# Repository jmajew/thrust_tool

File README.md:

# ThrustTool #

The ThrustTool is a DIY tool for measurements of an electric motor with propeller.
It allows to measure thrust, torque, rotation speed, battery voltage and current.

The project is by no means finished (especially firmware thrust++ and ThrustApp). However in current stage it works quite well allowing to obtain the results
(e.g., see auto generated report (in latex) [T-Motor F1507 with t3140 propeller](ThrustApp/data/tmotor-f1507/f1507_t3140_4s.pdf)).

### The project includes:

* [the 3d-printed tool](Doc/Tool.md)
* [custom board based on STM32 F401 mcu](Doc/Board.md)
* [firmware for the custom board](Doc/Firmware.md)
* [QT application for measurement managing and reporting](Doc/ThrustApp.md)

### 3D render of the tool

## Warning ##

The project is delivered as is. All responsibilities lies on the side of the user. 
Remember to take adequate security measures when testing any motor (especially powerful one).

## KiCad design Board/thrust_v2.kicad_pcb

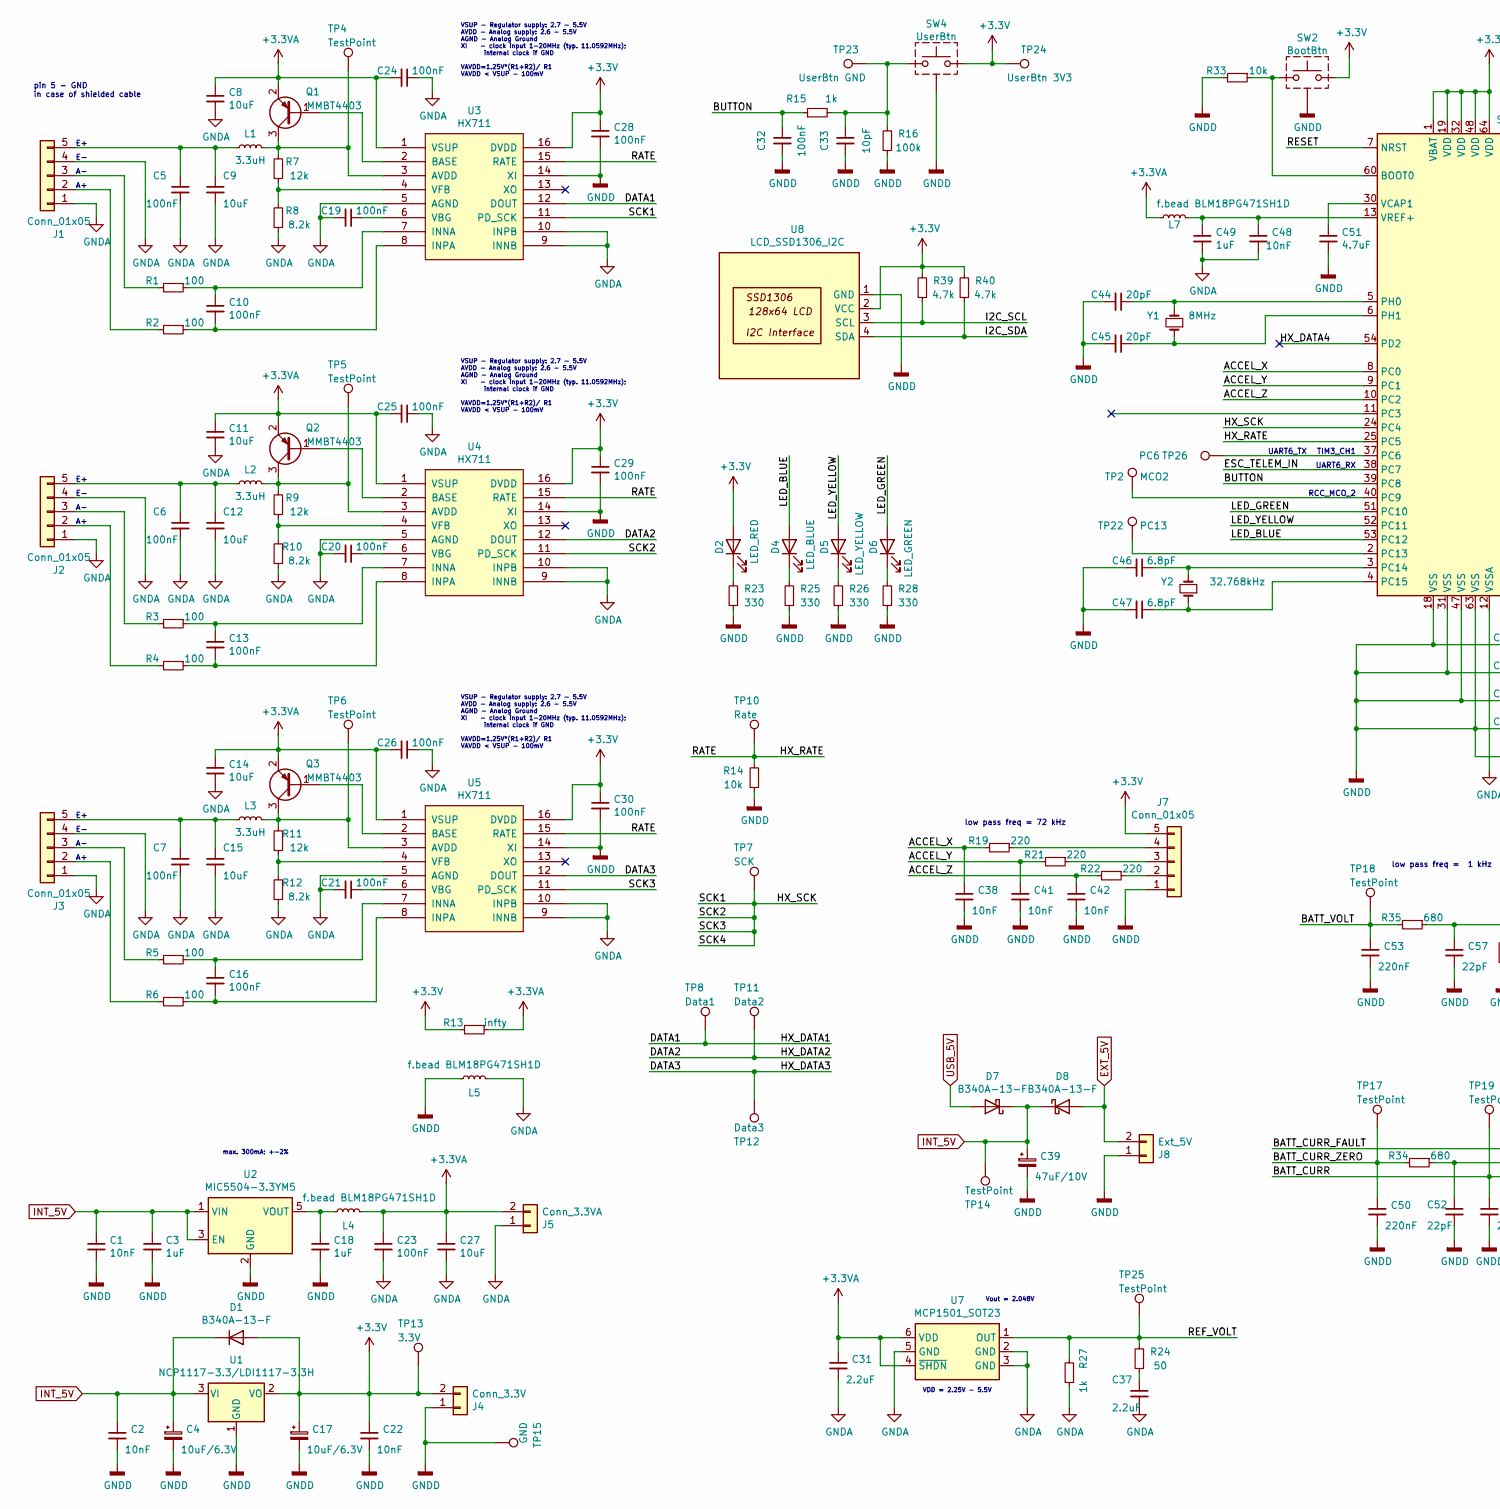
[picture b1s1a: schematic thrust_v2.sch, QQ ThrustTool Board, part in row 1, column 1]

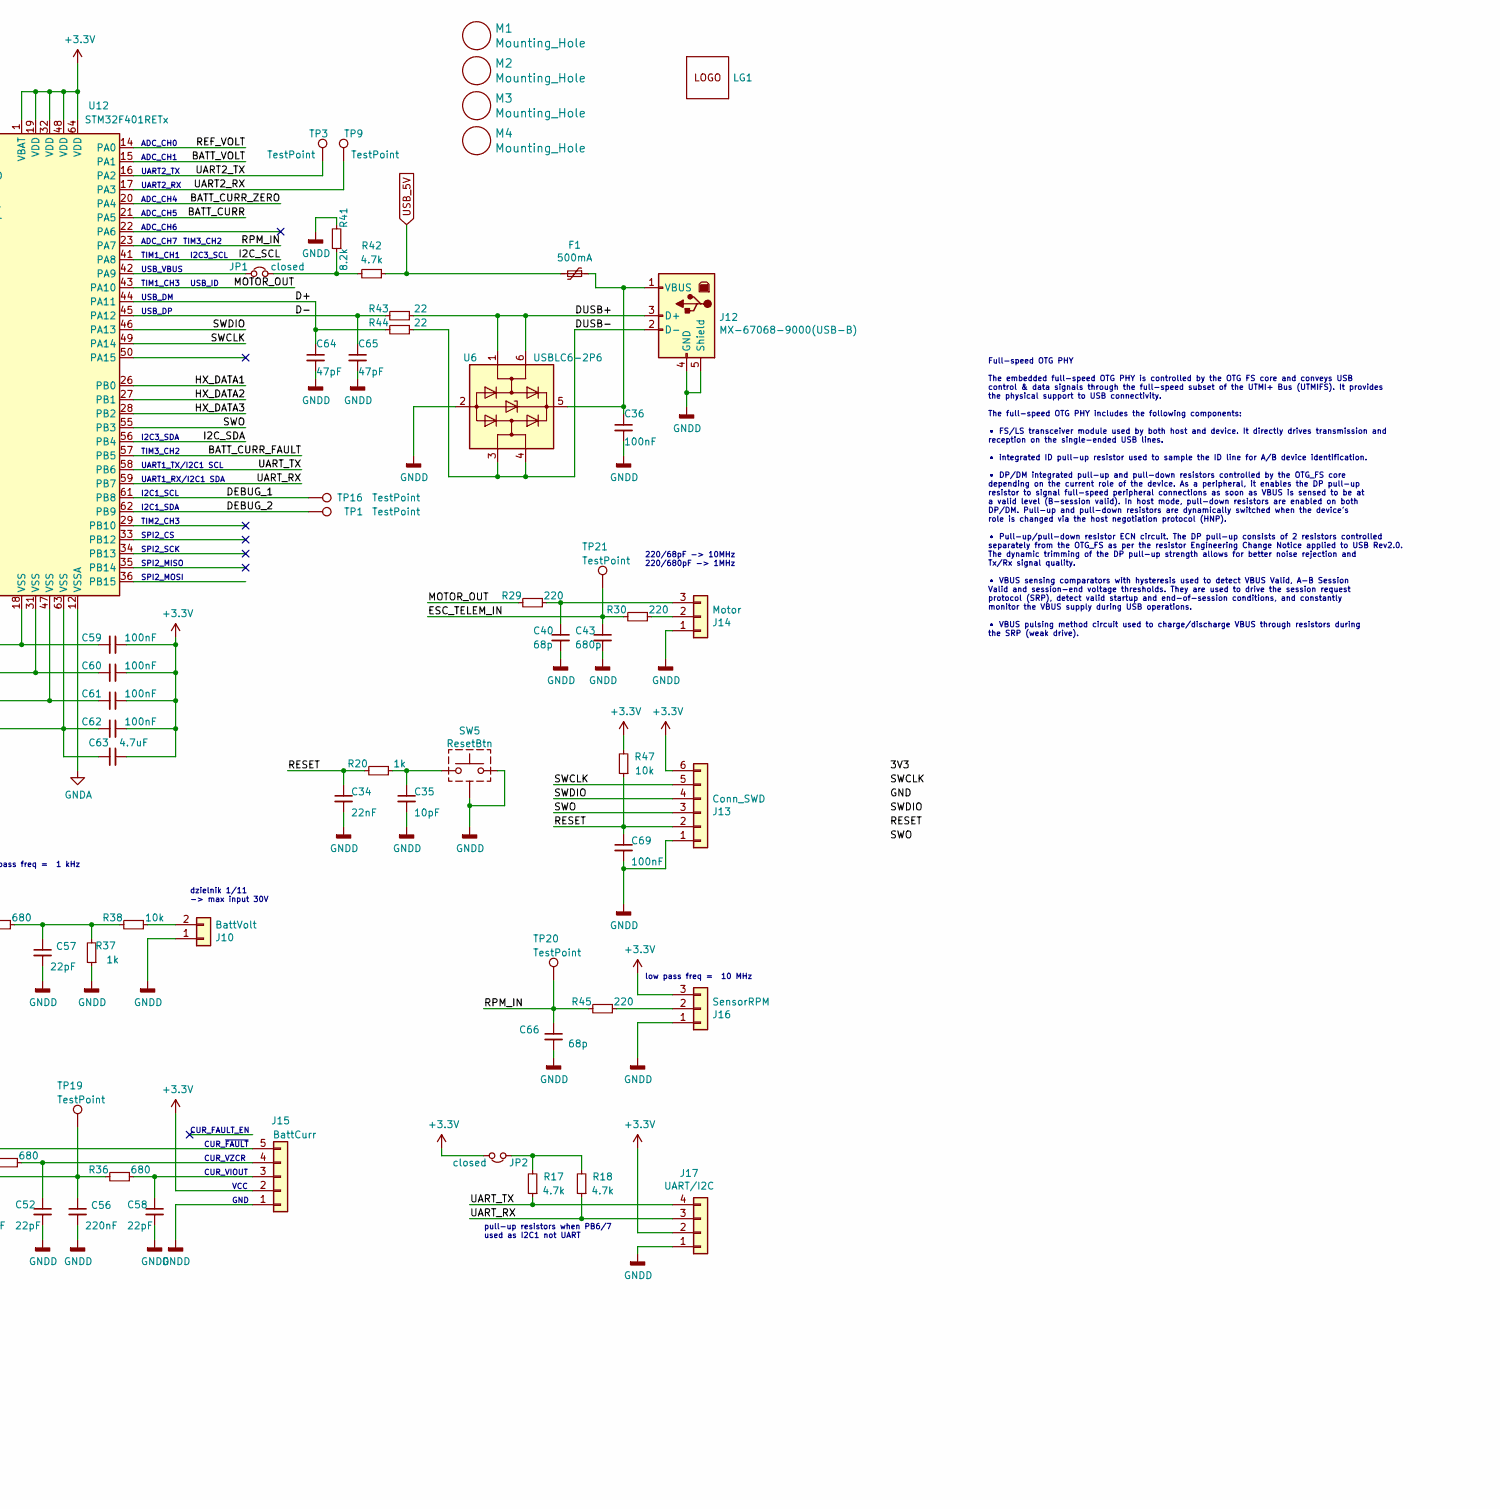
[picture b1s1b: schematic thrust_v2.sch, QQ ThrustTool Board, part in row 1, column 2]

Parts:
C1, C2, C22, C38, C41, C42, C48: 10nF; C_0603_1608Metric_Pad1.08x0.95mm_HandSolder
C3, C18, C49: 1uF; C_0603_1608Metric_Pad1.08x0.95mm_HandSolder
C4, C17: 10uF/6.3V; CP_EIA-3528-21_Kemet-B_Pad1.50x2.35mm_HandSolder
C5, C6, C7, C10, C13, C16, C19, C20, C21, C23, C24, C25, C26, C28, C29, C30, C32, C36, C59, C60, C61, C62, C69: 100nF; C_0603_1608Metric_Pad1.08x0.95mm_HandSolder
C8, C9, C11, C12, C14, C15, C27: 10uF; C_0603_1608Metric_Pad1.08x0.95mm_HandSolder
C31, C37: 2.2uF; C_0603_1608Metric_Pad1.08x0.95mm_HandSolder
C33, C35: 10pF; C_0603_1608Metric_Pad1.08x0.95mm_HandSolder
C34: 22nF; C_0603_1608Metric_Pad1.08x0.95mm_HandSolder
C39: 47uF/10V; CP_EIA-3528-21_Kemet-B_Pad1.50x2.35mm_HandSolder
C40, C66: 68p; C_0603_1608Metric_Pad1.08x0.95mm_HandSolder
C43: 680p; C_0603_1608Metric_Pad1.08x0.95mm_HandSolder
C44, C45: 20pF; C_0603_1608Metric_Pad1.08x0.95mm_HandSolder
C46, C47: 6.8pF; C_0603_1608Metric_Pad1.08x0.95mm_HandSolder
C50, C53, C56: 220nF; C_0603_1608Metric_Pad1.08x0.95mm_HandSolder
C51, C63: 4.7uF; C_0603_1608Metric_Pad1.08x0.95mm_HandSolder
C52, C57, C58: 22pF; C_0603_1608Metric_Pad1.08x0.95mm_HandSolder
C64, C65: 47pF; C_0603_1608Metric_Pad1.08x0.95mm_HandSolder
D1, D7, D8: B340A-13-F; D_SMA
D2: LED_RED; LED_0603_1608Metric_Pad1.05x0.95mm_HandSolder
D4: LED_BLUE; LED_0603_1608Metric_Pad1.05x0.95mm_HandSolder
D5: LED_YELLOW; LED_0603_1608Metric_Pad1.05x0.95mm_HandSolder
D6: LED_GREEN; LED_0603_1608Metric_Pad1.05x0.95mm_HandSolder
F1: 500mA; Fuse_0805_2012Metric_Pad1.15x1.40mm_HandSolder
J1, J2, J3, J7: Conn_01x05; PinHeader_1x05_P2.54mm_Vertical
J4: Conn_3.3V; PinHeader_1x02_P2.54mm_Vertical
J5: Conn_3.3VA; PinHeader_1x02_P2.54mm_Vertical
J8: Ext_5V; PinHeader_1x02_P2.54mm_Vertical
J10: BattVolt; PinHeader_1x02_P2.54mm_Vertical
J12: MX-67068-9000(USB-B); USB_B_OST_USB-B1HSxx_Horizontal_mod
J13: Conn_SWD; PinHeader_1x06_P2.54mm_Vertical
J14: Motor; PinHeader_1x03_P2.54mm_Vertical
J15: BattCurr; PinHeader_1x05_P2.54mm_Vertical
J16: SensorRPM; PinHeader_1x03_P2.54mm_Vertical
J17: UART/I2C; PinHeader_1x04_P2.54mm_Vertical
JP1, JP2: closed; SolderJumper-2_P1.3mm_Open_TrianglePad1.0x1.5mm
L1, L2, L3: 3.3uH; L_0603_1608Metric_Pad1.05x0.95mm_HandSolder
L4, L5, L7: f.bead BLM18PG471SH1D; L_0603_1608Metric_Pad1.05x0.95mm_HandSolder
LG1: Logo_1; LOGO_QX4_knot_circ2_24mm
M1, M2, M3, M4: Mounting_Hole; MountingHole_3.2mm_M3
Q1, Q2, Q3: MMBT4403; SOT-23
R1, R2, R3, R4, R5, R6: 100; R_0603_1608Metric_Pad0.98x0.95mm_HandSolder
R7, R9, R11: 12k; R_0603_1608Metric_Pad0.98x0.95mm_HandSolder
R8, R10, R12, R41: 8.2k; R_0603_1608Metric_Pad0.98x0.95mm_HandSolder
R13: infty; R_0603_1608Metric_Pad0.98x0.95mm_HandSolder
R14, R33, R38, R47: 10k; R_0603_1608Metric_Pad0.98x0.95mm_HandSolder
R15, R20, R27, R37: 1k; R_0603_1608Metric_Pad0.98x0.95mm_HandSolder
R16: 100k; R_0603_1608Metric_Pad0.98x0.95mm_HandSolder
R17, R18, R39, R40, R42: 4.7k; R_0603_1608Metric_Pad0.98x0.95mm_HandSolder
R19, R21, R22, R29, R30, R45: 220; R_0603_1608Metric_Pad0.98x0.95mm_HandSolder
R23, R25, R26, R28: 330; R_0603_1608Metric_Pad0.98x0.95mm_HandSolder
R24: 50; R_0603_1608Metric_Pad0.98x0.95mm_HandSolder
R34, R35, R36: 680; R_0603_1608Metric_Pad0.98x0.95mm_HandSolder
R43, R44: 22; R_0603_1608Metric_Pad0.98x0.95mm_HandSolder
SW2: BootBtn; SW_Push_1P1T-SH_NO_CK_KMR2xxG
SW4: UserBtn; SW_SPST_Panasonic_EVQPL_3PL_5PL_PT_A15
SW5: ResetBtn; SW_Push_1P1T-SH_NO_CK_KMR2xxG
TP1, TP3, TP9, TP14, TP16, TP17, TP18, TP19, TP20, TP21: TestPoint; TestPoint_Pad_1.5x1.5mm
TP2: MCO2; TestPoint_Pad_1.5x1.5mm
TP4, TP5, TP6, TP25: TestPoint; TestPoint_Pad_D1.0mm
TP7: SCK; TestPoint_Pad_1.5x1.5mm
TP8: Data1; TestPoint_Pad_1.5x1.5mm
TP10: Rate; TestPoint_Pad_1.5x1.5mm
TP11: Data2; TestPoint_Pad_1.5x1.5mm
TP12: Data3; TestPoint_Pad_1.5x1.5mm
TP13: 3.3V; TestPoint_Pad_1.5x1.5mm
TP15: GND; TestPoint_Pad_1.5x1.5mm
TP22: PC13; TestPoint_Pad_1.5x1.5mm
TP23: UserBtn GND; TestPoint_Pad_1.5x1.5mm
TP24: UserBtn 3V3; TestPoint_Pad_1.5x1.5mm
TP26: PC6; TestPoint_Pad_1.5x1.5mm
U1: NCP1117-3.3/LDI1117-3.3H; SOT-223-3_TabPin2
U2: MIC5504-3.3YM5; SOT-23-5
U3, U4, U5: HX711; SOIC-16_3.9x9.9mm_P1.27mm
U6: USBLC6-2P6; SOT-23-6
U7: MCP1501_SOT23; SOT-23-6
U8: LCD_SSD1306_I2C; PinHeader_1x04_P2.54mm_Vertical
U12: STM32F401RETx; LQFP-64_10x10mm_P0.5mm
Y1: 8MHz; Crystal_HC49-4H_Vertical
Y2: 32.768kHz; ABS25

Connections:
+3.3VA: C8.1, C11.1, C14.1, C23.1, C24.2, C25.2, C26.2, C27.1, C31.1, J5.2, L4.2, L7.1, Q1.2 (E), Q2.2 (E), Q3.2 (E), R13.1, U3.1 (VSUP), U4.1 (VSUP), U5.1 (VSUP), U7.4 (~SHDN), U7.6 (VDD)
+3V3: C17.1, C22.1, C28.1, C29.1, C30.1, C59.1, C60.1, C61.1, C62.1, C63.1, D1.2 (A), D2.2 (A), J4.2, J7.5, J13.6, J15.2, J16.3, J17.2, JP2.2, R13.2, R39.2, R40.2, R47.2, SW2.2, SW4.2, TP13.1, TP24.1, U1.2 (VO), U3.16 (DVDD), U4.16 (DVDD), U5.16 (DVDD), U8.2 (VCC), U12.1 (VBAT), U12.19 (VDD), U12.32 (VDD), U12.48 (VDD), U12.64 (VDD)
/ACCEL_X: C38.1, R19.2, U12.8 (PC0)
/ACCEL_Y: C41.1, R21.2, U12.9 (PC1)
/ACCEL_Z: C42.1, R22.2, U12.10 (PC2)
/BATT_CURR: C56.1, R36.2, TP19.1, U12.21 (PA5)
/BATT_CURR_FAULT: J15.5, U12.57 (PB5)
/BATT_CURR_ZERO: C50.1, R34.2, TP17.1, U12.20 (PA4)
/BATT_VOLT: C53.1, R35.2, TP18.1, U12.15 (PA1)
/BUTTON: C32.1, R15.1, U12.39 (PC8)
/D+: C64.1, R44.2, U12.44 (PA11)
/D-: C65.1, R43.2, U12.45 (PA12)
/DATA1: TP8.1, U3.12 (DOUT), U12.26 (PB0)
/DATA2: TP11.1, U4.12 (DOUT), U12.27 (PB1)
/DATA3: TP12.1, U5.12 (DOUT), U12.28 (PB2)
/DEBUG_1: TP16.1, U12.61 (PB8)
/DEBUG_2: TP1.1, U12.62 (PB9)
/DUSB+: J12.3 (D+), R43.1, U6.1 (I/O1), U6.6 (I/O1)
/DUSB-: J12.2 (D-), R44.1, U6.3 (I/O2), U6.4 (I/O2)
/ESC_TELEM_IN: C43.1, R30.2, TP21.1, U12.38 (PC7)
/HX_DATA4: U12.54 (PD2)
/HX_RATE: R14.2, TP10.1, U3.15 (RATE), U4.15 (RATE), U5.15 (RATE), U12.25 (PC5)
/HX_SCK: TP7.1, U3.11 (PD_SCK), U4.11 (PD_SCK), U5.11 (PD_SCK), U12.24 (PC4)
/I2C_SCL: R39.1, U8.3 (SCL), U12.41 (PA8)
/I2C_SDA: R40.1, U8.4 (SDA), U12.56 (PB4)
/LED_BLUE: D4.2 (A), U12.53 (PC12)
/LED_GREEN: D6.2 (A), U12.51 (PC10)
/LED_YELLOW: D5.2 (A), U12.52 (PC11)
/MOTOR_OUT: R29.2, U12.43 (PA10)
/REF_VOLT: R24.2, R27.2, TP25.1, U7.1 (OUT), U12.14 (PA0)
/RESET: C34.1, C69.1, J13.2, R20.2, R47.1, U12.7 (NRST)
/RPM_IN: C66.1, R45.2, TP20.1, U12.23 (PA7)
/SWCLK: J13.5, U12.49 (PA14)
/SWDIO: J13.4, U12.46 (PA13)
/SWO: J13.3, U12.55 (PB3)
/UART2_RX: TP9.1, U12.17 (PA3)
/UART2_TX: TP3.1, U12.16 (PA2)
/UART_RX: J17.3, R18.1, U12.59 (PB7)
/UART_TX: J17.4, R17.1, U12.58 (PB6)
EXT_5V: D8.2 (A), J8.2
GNDA: C5.2, C6.2, C7.2, C8.2, C9.2, C11.2, C12.2, C14.2, C15.2, C19.2, C20.2, C21.2, C23.2, C24.1, C25.1, C26.1, C27.2, C31.2, C37.2, C48.2, C49.2, J1.1, J1.4, J2.1, J2.4, J3.1, J3.4, J5.1, L5.2, R8.1, R10.1, R12.1, R27.1, U3.5 (AGND), U3.9 (INNB), U3.10 (INPB), U4.5 (AGND), U4.9 (INNB), U4.10 (INPB), U5.5 (AGND), U5.9 (INNB), U5.10 (INPB), U7.2 (GND), U7.3 (GND), U7.5 (GND), U12.12 (VSSA)
GNDD: C1.2, C2.2, C3.2, C4.2, C17.2, C18.2, C22.2, C28.2, C29.2, C30.2, C32.2, C33.2, C34.2, C35.2, C36.2, C38.2, C39.2, C40.2, C41.2, C42.2, C43.2, C44.2, C45.2, C46.2, C47.2, C50.2, C51.2, C52.2, C53.2, C56.2, C57.2, C58.2, C59.2, C60.2, C61.2, C62.2, C63.2, C64.2, C65.2, C66.2, C69.2, J4.1, J7.1, J8.1, J10.1, J12.4 (GND), J12.5 (Shield), J13.1, J14.1, J15.1, J16.1, J17.1, L5.1, R14.1, R16.1, R23.1, R25.1, R26.1, R28.1, R33.2, R37.1, R41.2, SW2.SH (GND), SW4.0 (GND), SW5.2, SW5.SH (GND), TP15.1, U1.1 (GND), U2.2 (GND), U3.14 (XI), U4.14 (XI), U5.14 (XI), U6.2 (GND), U8.1 (GND), U12.18 (VSS), U12.31 (VSS), U12.47 (VSS), U12.63 (VSS)
INT_5V: C1.1, C2.1, C3.1, C4.1, C39.1, D1.1 (K), D7.1 (K), D8.1 (K), TP14.1, U1.3 (VI), U2.1 (VIN), U2.3 (EN)
unnamed: C5.1, C9.1, J1.5, L1.1
unnamed: C10.1, R1.1, U3.7 (INNA)
unnamed: C10.2, R2.1, U3.8 (INPA)
unnamed: C6.1, C12.1, J2.5, L2.1
unnamed: C13.1, R3.1, U4.7 (INNA)
unnamed: C13.2, R4.1, U4.8 (INPA)
unnamed: C7.1, C15.1, J3.5, L3.1
unnamed: C16.1, R5.1, U5.7 (INNA)
unnamed: C16.2, R6.1, U5.8 (INPA)
unnamed: C18.1, L4.1, U2.5 (VOUT)
unnamed: C19.1, U3.6 (VBG)
unnamed: C20.1, U4.6 (VBG)
unnamed: C21.1, U5.6 (VBG)
unnamed: C33.1, R15.2, R16.2, SW4.1, TP23.1
unnamed: C35.1, R20.1, SW5.1
unnamed: C36.1, F1.1, J12.1 (VBUS), U6.5 (VBUS)
unnamed: C37.1, R24.1
unnamed: C40.1, J14.3, R29.1
unnamed: C44.1, U12.5 (PH0), Y1.2
unnamed: C45.1, U12.6 (PH1), Y1.1
unnamed: C46.1, U12.3 (PC14), Y2.2
unnamed: C47.1, U12.4 (PC15), Y2.1
unnamed: C48.1, C49.1, L7.2, U12.13 (VREF+)
unnamed: C51.1, U12.30 (VCAP1)
unnamed: C52.1, J15.4, R34.1
unnamed: C57.1, R35.1, R37.2, R38.2
unnamed: C58.1, J15.3, R36.1
unnamed: D2.1 (K), R23.2
unnamed: D4.1 (K), R25.2
unnamed: D5.1 (K), R26.2
unnamed: D6.1 (K), R28.2
unnamed: J1.2, R2.2
unnamed: J1.3, R1.2
unnamed: J2.2, R4.2
unnamed: J2.3, R3.2
unnamed: J3.2, R6.2
unnamed: J3.3, R5.2
unnamed: J7.2, R22.1
unnamed: J7.3, R21.1
unnamed: J7.4, R19.1
unnamed: J10.2, R38.1
unnamed: J14.2, R30.1
unnamed: J16.2, R45.1
unnamed: JP1.1, U12.42 (PA9)
unnamed: JP1.2, R41.1, R42.2
unnamed: JP2.1, R17.2, R18.2
unnamed: L1.2, Q1.3 (C), R7.2, TP4.1, U3.3 (AVDD)
unnamed: L2.2, Q2.3 (C), R9.2, TP5.1, U4.3 (AVDD)
unnamed: L3.2, Q3.3 (C), R11.2, TP6.1, U5.3 (AVDD)
unnamed: Q1.1 (B), U3.2 (BASE)
unnamed: Q2.1 (B), U4.2 (BASE)
unnamed: Q3.1 (B), U5.2 (BASE)
unnamed: R7.1, R8.2, U3.4 (VFB)
unnamed: R9.1, R10.2, U4.4 (VFB)
unnamed: R11.1, R12.2, U5.4 (VFB)
unnamed: R33.1, SW2.1, U12.60 (BOOT0)
unnamed: TP2.1, U12.40 (PC9)
unnamed: TP22.1, U12.2 (PC13)
unnamed: TP26.1, U12.37 (PC6)
USB_5V: D7.2 (A), F1.2, R42.1

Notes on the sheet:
Vout = 2.048V
VDD = 2.25V - 5.5V
max. 300mA; +-2%
VSUP - Regulator supply: 2.7 - 5.5V AVDD - Analog supply: 2.6 - 5.5V AGND - Analog Ground XI - clock input 1-20MHz (typ. 11.0592MHz); internal clock if GND VAVDD=1.25V*(R1+R2)/ R1 VAVDD < VSUP - 100mV
dzielnik 1/11 -> max input 30V
CUR_FAULT_EN
CUR_~FAULT
CUR_VZCR
CUR_VIOUT
VCC
GND
pin 5 - GND in case of shielded cable
I2C3_SDA
I2C3_SCL
TIM1_CH3
SPI2_MOSI
SPI2_MISO
SPI2_SCK
RCC_MCO_2
ADC_CH5
UART2_RX
UART2_TX
TIM3_CH1
UART6_RX
TIM1_CH1
ADC_CH7
ADC_CH6
ADC_CH4
ADC_CH1
ADC_CH0
I2C1_SDA
I2C1_SCL
USB_ID
UART1_TX/I2C1 SCL
UART1_RX/I2C1 SDA
USB_VBUS
USB_DM
USB_DP
pull-up resistors when PB6/7 used as I2C1 not UART
Full-speed OTG PHY The embedded full-speed OTG PHY is controlled by the OTG FS core and conveys USB control & data signals through the full-speed subset of the UTMI+ Bus (UTMIFS). It provides the physical support to USB connectivity. The full-speed OTG PHY includes the following components: • FS/LS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

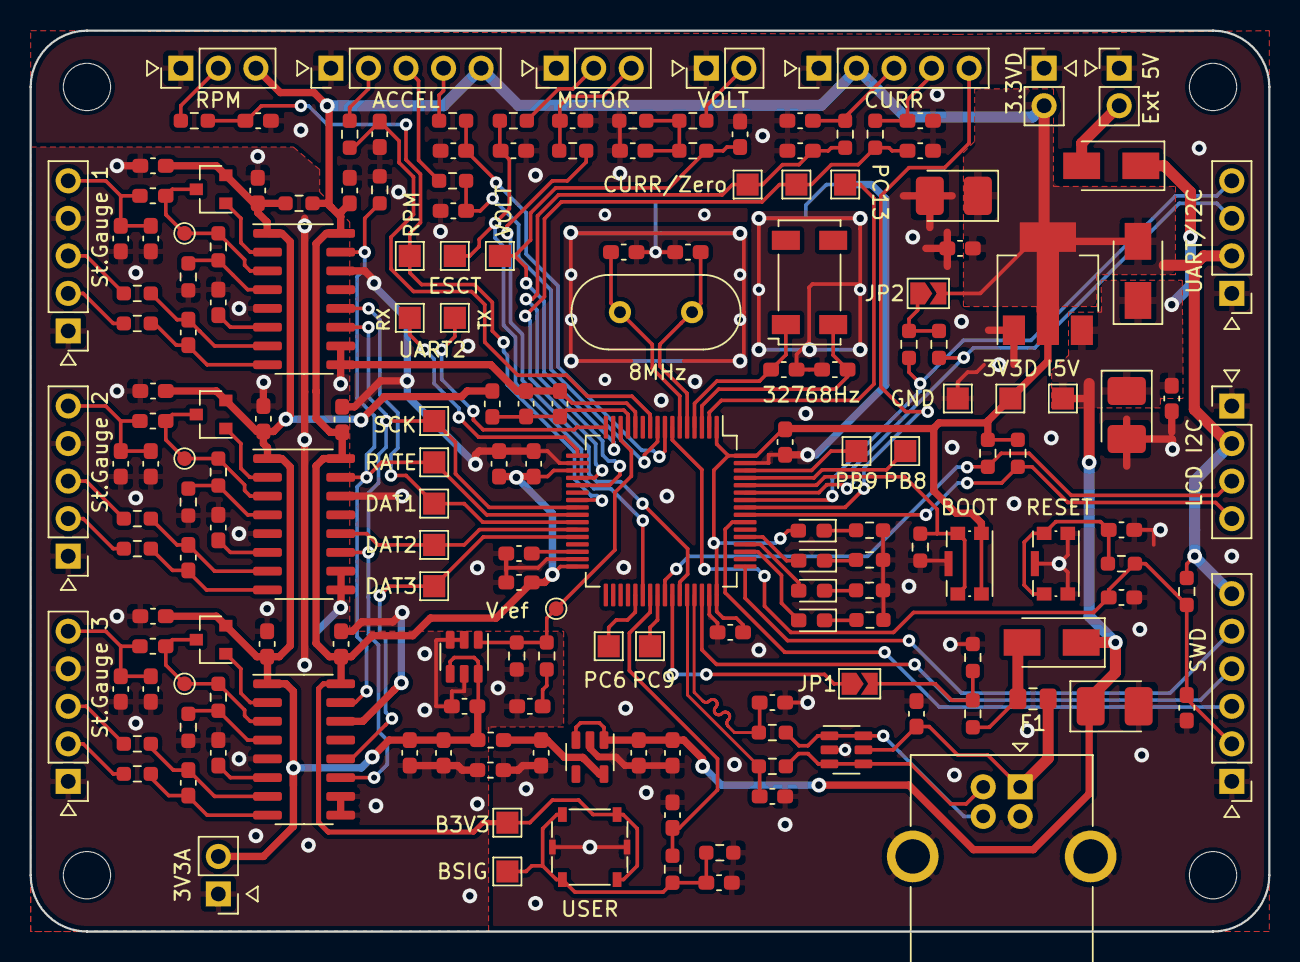
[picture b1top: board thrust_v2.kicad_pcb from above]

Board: 2 copper layers, 83.8 x 61.0 mm, 187 parts (1 on the bottom side), 102 nets.

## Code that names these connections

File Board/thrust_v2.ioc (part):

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Mcu.Name=STM32F401R(D-E)Tx
Mcu.Package=LQFP64
Mcu.UserName=STM32F401RETx
PA0-WKUP.GPIOParameters=GPIO_Label
PA0-WKUP.GPIO_Label=ADC_REF_VOLT
PA0-WKUP.Signal=ADCx_IN0
PA1.GPIOParameters=GPIO_Label
PA1.GPIO_Label=ADC_BATT_VOLT
PA1.Signal=ADCx_IN1
PA10.GPIOParameters=GPIO_Label
PA10.GPIO_Label=TIM1_CH3  MOTOR_Output
PA10.Signal=S_TIM1_CH3
PA11.Mode=Device_Only
PA11.Signal=USB_OTG_FS_DM
PA12.Mode=Device_Only
PA12.Signal=USB_OTG_FS_DP
PA13.Mode=Trace_Asynchronous_SW
PA13.Signal=SYS_JTMS-SWDIO
PA14.Mode=Trace_Asynchronous_SW
PA14.Signal=SYS_JTCK-SWCLK
PA2.Mode=Asynchronous
PA2.Signal=USART2_TX
PA3.Mode=Asynchronous
PA3.Signal=USART2_RX
PA4.GPIOParameters=GPIO_Label
PA4.GPIO_Label=ADC_BATT_CURR_ZERO
PA4.Signal=ADCx_IN4
PA5.GPIOParameters=GPIO_Label
PA5.GPIO_Label=ADC_BATT_CURR
PA5.Signal=ADCx_IN5
PA7.GPIOParameters=GPIO_Label
PA7.GPIO_Label=TIM3_CH2 RPM_IN
PA7.Signal=S_TIM3_CH2
PA8.GPIOParameters=GPIO_Pu
PA8.GPIO_Pu=GPIO_PULLUP
PA8.Mode=I2C
PA8.Signal=I2C3_SCL
PA9.Mode=Activate_VBUS
PA9.Signal=USB_OTG_FS_VBUS
PB0.GPIOParameters=GPIO_Label
PB0.GPIO_Label=HX_DATA1_Input
PB0.Signal=GPIO_Input
PB1.GPIOParameters=GPIO_Label
PB1.GPIO_Label=HX_DATA2_Input
PB1.Signal=GPIO_Input
PB15.GPIOParameters=GPIO_Label
PB15.GPIO_Label=BUTTON
PB15.Signal=GPIO_Input
PB2.GPIOParameters=GPIO_Label
PB2.GPIO_Label=HX_DATA3_Input
PB2.Signal=GPIO_Input
PB3.Mode=Trace_Asynchronous_SW
PB3.Signal=SYS_JTDO-SWO
PB4.GPIOParameters=GPIO_Pu
PB4.GPIO_Pu=GPIO_PULLUP
PB4.Mode=I2C
PB4.Signal=I2C3_SDA
PB5.GPIOParameters=GPIO_Label
PB5.GPIO_Label=BAT_CURR_FAULT
PB5.Signal=GPIO_Input
PB6.Mode=Asynchronous
PB6.Signal=USART1_TX
PB7.Mode=Asynchronous
PB7.Signal=USART1_RX
PB8.GPIOParameters=GPIO_Label
PB8.GPIO_Label=DEBUG_1_Output
PB8.Signal=GPIO_Output
PB9.GPIOParameters=GPIO_Label
PB9.GPIO_Label=DEBUG_2_Ouptur
PB9.Signal=GPIO_Output
PC0.GPIOParameters=GPIO_Label
PC0.GPIO_Label=ADC ACCEL_X
PC0.Signal=ADCx_IN10
PC1.GPIOParameters=GPIO_Label
PC1.GPIO_Label=ADC ACCEL_Y
PC1.Signal=ADCx_IN11
PC10.GPIOParameters=GPIO_Label
PC10.GPIO_Label=LED_GREEN
PC10.Signal=GPIO_Output
PC11.GPIOParameters=GPIO_Label
PC11.GPIO_Label=LED_YELLOW
PC11.Signal=GPIO_Output
PC12.GPIOParameters=GPIO_Label
PC12.GPIO_Label=LED_BLUE
PC12.Signal=GPIO_Output
PC13-ANTI_TAMP.GPIOParameters=GPIO_Label
PC13-ANTI_TAMP.GPIO_Label=TEST_PC13
PC13-ANTI_TAMP.Signal=GPIO_Output
PC14-OSC32_IN.Mode=LSE-External-Oscillator
PC14-OSC32_IN.Signal=RCC_OSC32_IN
PC15-OSC32_OUT.Mode=LSE-External-Oscillator
PC15-OSC32_OUT.Signal=RCC_OSC32_OUT
PC2.GPIOParameters=GPIO_Label
PC2.GPIO_Label=ADC ACCEL_Z
PC2.Signal=ADCx_IN12
PC4.GPIOParameters=GPIO_Label
PC4.GPIO_Label=HX_SCK_Output
PC4.Signal=GPIO_Output
PC5.GPIOParameters=GPIO_Label
PC5.GPIO_Label=HX_RATE_Output
PC5.Signal=GPIO_Output
PC6.Mode=Asynchronous
PC6.Signal=USART6_TX
PC7.GPIOParameters=GPIO_Label
PC7.GPIO_Label=UART6_RX ESC_TELEM_Input
PC7.Mode=Asynchronous
PC7.Signal=USART6_RX
PC8.GPIOParameters=GPIO_Label
PC8.GPIO_Label=BUTTON
PC8.Signal=GPIO_Input
PC9.Mode=Clock-out-2
PC9.Signal=RCC_MCO_2
PH0\ -\ OSC_IN.Mode=HSE-External-Oscillator
PH0\ -\ OSC_IN.Signal=RCC_OSC_IN
PH1\ -\ OSC_OUT.Mode=HSE-External-Oscillator
PH1\ -\ OSC_OUT.Signal=RCC_OSC_OUT
RCC.HSE_VALUE=8000000
RCC.SYSCLKFreq_VALUE=84000000
RCC.SYSCLKSource=RCC_SYSCLKSOURCE_PLLCLK
board=custom

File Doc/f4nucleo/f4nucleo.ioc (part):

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Mcu.Name=STM32F401R(D-E)Tx
Mcu.Package=LQFP64
Mcu.UserName=STM32F401RETx
PA0-WKUP.GPIOParameters=GPIO_Label
PA0-WKUP.GPIO_Label=ADC_REF_VOLT
PA0-WKUP.Signal=ADCx_IN0
PA1.GPIOParameters=GPIO_Label
PA1.GPIO_Label=ADC_BATT_VOLT
PA1.Signal=ADCx_IN1
PA10.GPIOParameters=GPIO_Label
PA10.GPIO_Label=TIM1_CH3 MOTOR_OUT
PA10.Signal=S_TIM1_CH3
PA13.GPIOParameters=GPIO_Label
PA13.GPIO_Label=TMS
PA13.Mode=Trace_Asynchronous_SW
PA13.Signal=SYS_JTMS-SWDIO
PA14.GPIOParameters=GPIO_Label
PA14.GPIO_Label=TCK
PA14.Mode=Trace_Asynchronous_SW
PA14.Signal=SYS_JTCK-SWCLK
PA2.GPIOParameters=GPIO_Speed,GPIO_PuPd,GPIO_Label,GPIO_Mode
PA2.GPIO_Label=USART_TX
PA2.GPIO_Mode=GPIO_MODE_AF_PP
PA2.GPIO_PuPd=GPIO_NOPULL
PA2.GPIO_Speed=GPIO_SPEED_FREQ_LOW
PA2.Mode=Asynchronous
PA2.Signal=USART2_TX
PA3.GPIOParameters=GPIO_Speed,GPIO_PuPd,GPIO_Label,GPIO_Mode
PA3.GPIO_Label=USART_RX
PA3.GPIO_Mode=GPIO_MODE_AF_PP
PA3.GPIO_PuPd=GPIO_NOPULL
PA3.GPIO_Speed=GPIO_SPEED_FREQ_LOW
PA3.Mode=Asynchronous
PA3.Signal=USART2_RX
PA4.GPIOParameters=GPIO_Label
PA4.GPIO_Label=ADC_BATT_CURR_ZERO
PA4.Signal=ADCx_IN4
PA5.GPIOParameters=GPIO_Speed,GPIO_PuPd,GPIO_Label,GPIO_Mode
PA5.GPIO_Label=LD2 [Green Led]
PA5.GPIO_Mode=GPIO_MODE_OUTPUT_PP
PA5.GPIO_PuPd=GPIO_NOPULL
PA5.GPIO_Speed=GPIO_SPEED_FREQ_LOW
PA5.Signal=GPIO_Output
PA6.GPIOParameters=GPIO_Label
PA6.GPIO_Label=ADC_BATT_CURR
PA6.Signal=ADCx_IN6
PA7.GPIOParameters=GPIO_Label
PA7.GPIO_Label=TIM3_CH2 RPM_IN
PA7.Signal=S_TIM3_CH2
PA8.Mode=I2C
PA8.Signal=I2C3_SCL
PB0.GPIOParameters=GPIO_Label
PB0.GPIO_Label=HK_DATA1
PB0.Signal=GPIO_Input
PB1.GPIOParameters=GPIO_Label
PB1.GPIO_Label=HK_DATA2
PB1.Signal=GPIO_Input
PB2.GPIOParameters=GPIO_Label
PB2.GPIO_Label=HK_DATA3
PB2.Signal=GPIO_Input
PB3.GPIOParameters=GPIO_Label
PB3.GPIO_Label=SWO
PB3.Mode=Trace_Asynchronous_SW
PB3.Signal=SYS_JTDO-SWO
PB4.Mode=I2C
PB4.Signal=I2C3_SDA
PB5.GPIOParameters=GPIO_Label
PB5.GPIO_Label=BAT_CURR_FAULT
PB5.Signal=GPIO_Input
PB6.Mode=Asynchronous
PB6.Signal=USART1_TX
PB7.Mode=Asynchronous
PB7.Signal=USART1_RX
PB8.GPIOParameters=GPIO_Label
PB8.GPIO_Label=DEBUG_1
PB8.Signal=GPIO_Output
PB9.GPIOParameters=GPIO_Label
PB9.GPIO_Label=DEBUG_2
PB9.Signal=GPIO_Output
PC0.GPIOParameters=GPIO_Label
PC0.GPIO_Label=ADC_ACCEL_X
PC0.Signal=ADCx_IN10
PC1.GPIOParameters=GPIO_Label
PC1.GPIO_Label=ADC_ACCEL_Y
PC1.Signal=ADCx_IN11
PC10.GPIOParameters=GPIO_Label
PC10.GPIO_Label=GREEN
PC10.Signal=GPIO_Output
PC11.GPIOParameters=GPIO_Label
PC11.GPIO_Label=YELLOW
PC11.Signal=GPIO_Output
PC12.GPIOParameters=GPIO_Label
PC12.GPIO_Label=BLUE
PC12.Signal=GPIO_Output
PC13-ANTI_TAMP.GPIOParameters=GPIO_PuPd,GPIO_Label,GPIO_ModeDefaultEXTI
PC13-ANTI_TAMP.GPIO_Label=B1 [Blue PushButton]
PC13-ANTI_TAMP.GPIO_ModeDefaultEXTI=GPIO_MODE_IT_FALLING
PC13-ANTI_TAMP.GPIO_PuPd=GPIO_NOPULL
PC13-ANTI_TAMP.Signal=GPXTI13
PC14-OSC32_IN.Mode=LSE-External-Oscillator
PC14-OSC32_IN.Signal=RCC_OSC32_IN
PC15-OSC32_OUT.Mode=LSE-External-Oscillator
PC15-OSC32_OUT.Signal=RCC_OSC32_OUT
PC2.GPIOParameters=GPIO_Label
PC2.GPIO_Label=ADC_ACCEL_Z
PC2.Signal=ADCx_IN12
PC4.GPIOParameters=GPIO_Label
PC4.GPIO_Label=HK_SCK_OUT
PC4.Signal=GPIO_Output
PC5.GPIOParameters=GPIO_Label
PC5.GPIO_Label=HK_RATE_OUT
PC5.Signal=GPIO_Output
PC6.Mode=Asynchronous
PC6.Signal=USART6_TX
PC7.Mode=Asynchronous
PC7.Signal=USART6_RX
PC8.GPIOParameters=GPIO_Label
PC8.GPIO_Label=BUTTON
PC8.Signal=GPIO_Input
PC9.Mode=Clock-out-2
PC9.Signal=RCC_MCO_2
PH0\ -\ OSC_IN.Mode=HSE-External-Clock-Source
PH0\ -\ OSC_IN.Signal=RCC_OSC_IN
PH1\ -\ OSC_OUT.Mode=HSE-External-Clock-Source
PH1\ -\ OSC_OUT.Signal=RCC_OSC_OUT
RCC.HSE_VALUE=8000000
RCC.SYSCLKFreq_VALUE=84000000
RCC.SYSCLKSource=RCC_SYSCLKSOURCE_PLLCLK
board=NUCLEO-F401RE
boardIOC=true

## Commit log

2022-04-16 initial import
2022-04-16 stl files for 3dprint added
2022-04-16 step files added
2022-04-16 doc wip
2022-04-18 board pics added
2022-04-18 boar .ioc updated
2022-04-19 fix curr_zero connection
2022-04-19 bugfix for incorrect curr_zero_pin
2022-04-19 board schematic updated
2022-04-24 settings tested; can be written to the flash using thrustapp
2022-04-24 pictures added
2022-04-25 f1507-t3140 results added
2022-04-25 rm old results
2022-04-25 bugfix for cell volt. in status bar
2022-04-26 app save/export dlg set default names
2022-05-01 bugfix for cfg. vbat correction; mn2206 + 3 blade prop. measurement added
2022-05-02 analyzer fix; new measerements for mn2206 added
2022-05-07 app asks before new doc; .gitignore added
2022-05-08 rep template wip
2022-05-08 tex templ updated; pdfs regenerated; mt2212 added
2022-05-09 mt2212 with prop 10x4.5 added
2022-05-13 starting new branch
2022-05-13 bugfix: unbalanced mutex
2022-05-14 sources of curr0 tested
2022-05-14 .th files converted to current version
2022-05-15 fw created new branch
2022-05-16 doc f4 pin mappings updated
2022-05-16 fw-nucleo project added
2022-05-18 fw nucleo testing remapped resources
2022-05-19 fw cmsis-dsp library added
2022-05-19 fw wip
2022-05-21 fw nucleo changes moved to thrust_board fw
2022-05-21 fw_thrust accel adc - first tests
2022-05-21 dsp added to fw_thrust
2022-09-11 fw TODO: sensor settings added
2022-09-11 fw TODO.md load cell calib. values added
2022-09-12 fw: stg gain fix
2022-09-15 wip: minor fixes; fw defaults for cfg changed
2022-09-16 new measurements added
2022-09-21 new measurement added
2022-09-22 new data added
2023-04-09 racestar-br2507s measurements added
2023-04-10 rstar br2507s 6x4x3 4s measuerments added
2023-04-10 updating data
2023-04-12 thapp: git info added to cmakefile
2023-04-12 thapp: wip
2023-04-13 current calibration revisited
2023-04-13 thapp: added thapp info to doc header
2023-04-21 chibios moved to lib; cfg files updated to the recent ver of ChibiOS.git
2023-05-18 new measurements and some corrections
2023-05-23 data rearanged
